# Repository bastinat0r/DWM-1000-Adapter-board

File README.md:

# Board to Interface with DWM1000 module from Decawave

Created by Sebastian Mai under CC-BY-SA 2.0 license.

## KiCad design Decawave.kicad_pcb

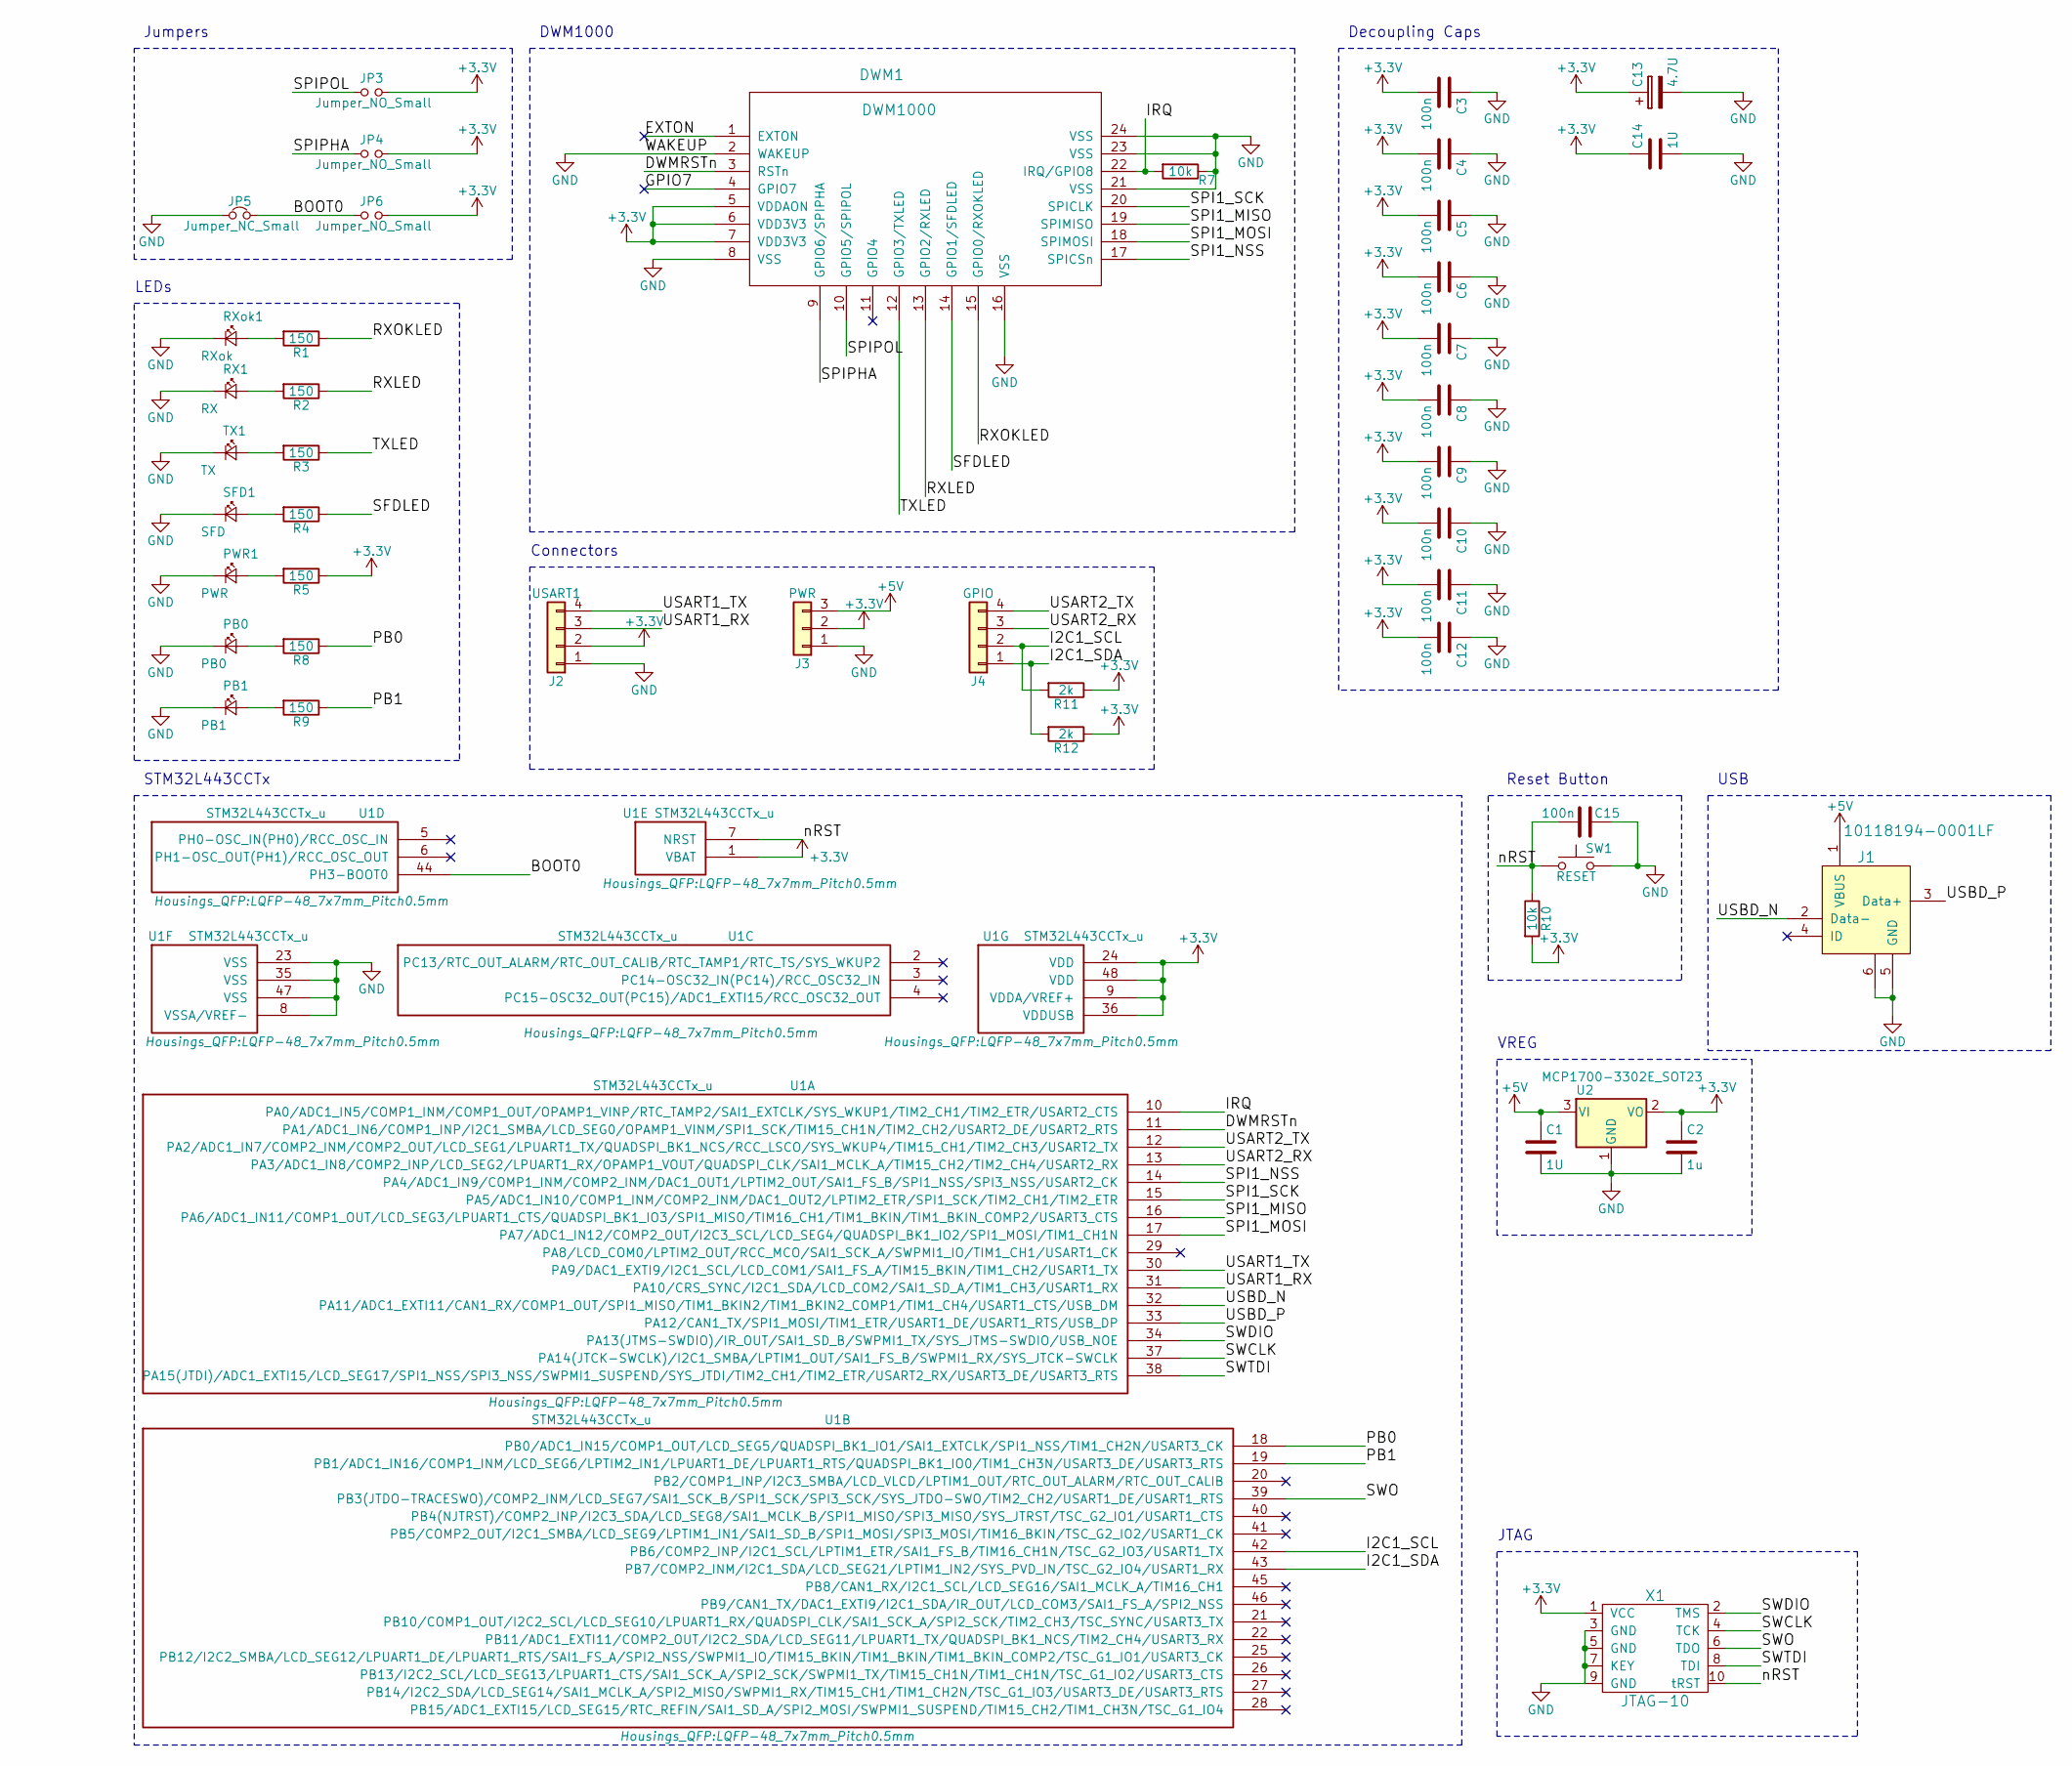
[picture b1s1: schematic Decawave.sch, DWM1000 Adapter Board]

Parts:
C1, C14: 1U; C_1206_HandSoldering
C2: 1u; C_1206_HandSoldering
C3, C4, C5, C6, C7, C8, C9, C10, C11, C12, C15: 100n; C_0603_HandSoldering
C13: 4.7U; CP_Tantalum_Case-A_EIA-3216-18_Hand
DWM1: DWM1000
J1: 10118194-0001LF; USB_Micro_B_Female_10118194-0001LF; MPN 10118194-0001LF; Digi-Key_PN 609-4618-1-ND
J2: USART1; Pin_Header_Straight_1x04_Pitch2.54mm
J3: PWR; Pin_Header_Straight_1x03_Pitch2.54mm
J4: GPIO; Pin_Header_Straight_1x04_Pitch2.54mm
JP3, JP4, JP6: Jumper_NO_Small; R_0402
JP5: Jumper_NC_Small; R_0402
PB0: PB0; LED_0805_HandSoldering
PB1: PB1; LED_0805_HandSoldering
PWR1: PWR; LED_0805_HandSoldering
R1, R2, R3, R4, R5, R8, R9: 150; R_0603_HandSoldering
R7, R10: 10k; R_0603_HandSoldering
R11, R12: 2k; R_0603_HandSoldering
RX1: RX; LED_0805_HandSoldering
RXok1: RXok; LED_0805_HandSoldering
SFD1: SFD; LED_0805_HandSoldering
SW1: RESET; SW_SPST_TL3342
TX1: TX; LED_0805_HandSoldering
U1: STM32L443CCTx_u; LQFP-48_7x7mm_Pitch0.5mm
U2: MCP1700-3302E_SOT23; SOT-23_Handsoldering
X1: JTAG-10; FTSH-105-XX-X-DV

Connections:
+3V3: C2.1, C3.2, C4.2, C5.2, C6.2, C7.2, C8.2, C9.2, C10.2, C11.2, C12.2, C13.1, C14.1, DWM1.5 (VDDAON), DWM1.6 (VDD3V3), DWM1.7 (VDD3V3), J2.2, J3.2, JP3.2, JP4.2, JP6.2, R5.1, R10.2, R11.1, R12.1, U1.1 (VBAT), U1.9 (VDDA/VREF+), U1.24 (VDD), U1.36 (VDDUSB), U1.48 (VDD), U2.2 (VO), X1.1 (VCC)
+5V: C1.1, J1.1 (VBUS), J3.3, U2.3 (VI)
/BOOT0: JP5.2, JP6.1, U1.44 (PH3-BOOT0)
/DWMRSTn: DWM1.3 (RSTn), U1.11 (PA1/ADC1_IN6/COMP1_INP/I2C1_SMBA/LCD_SE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)
/EXTON: DWM1.1 (EXTON)
/GPIO7: DWM1.4 (GPIO7)
/I2C1_SCL: J4.2, R11.2, U1.42 (PB6/COMP2_INP/I2C1_SCL/LPTIM1_ETR/SAI1_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)
/I2C1_SDA: J4.1, R12.2, U1.43 (PB7/COMP2_INM/I2C1_SDA/LCD_SEG21/LPTIM1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)
/IRQ: DWM1.22 (IRQ/GPIO8), R7.2, U1.10 (PA0/ADC1_IN5/COMP1_INM/COMP1_OUT/OPAMP1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)
/PB0: R8.1, U1.18 (PB0/ADC1_IN15/COMP1_OUT/LCD_SEG5/QUADSP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)
/PB1: R9.1, U1.19 (PB1/ADC1_IN16/COMP1_INM/LCD_SEG6/LPTIM2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)
/RXLED: DWM1.13 (GPIO2/RXLED), R2.1
/RXOKLED: DWM1.15 (GPIO0/RXOKLED), R1.1
/SFDLED: DWM1.14 (GPIO1/SFDLED), R4.1
/SPI1_MISO: DWM1.19 (SPIMISO), U1.16 (PA6/ADC1_IN11/COMP1_OUT/LCD_SEG3/LPUART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)
/SPI1_MOSI: DWM1.18 (SPIMOSI), U1.17 (PA7/ADC1_IN12/COMP2_OUT/I2C3_SCL/LCD_SE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)
/SPI1_NSS: DWM1.17 (SPICSn), U1.14 (PA4/ADC1_IN9/COMP1_INM/COMP2_INM/DAC1_O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)
/SPI1_SCK: DWM1.20 (SPICLK), U1.15 (PA5/ADC1_IN10/COMP1_INM/COMP2_INM/DAC1_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)
/SPIPHA: DWM1.9 (GPIO6/SPIPHA), JP4.1
/SPIPOL: DWM1.10 (GPIO5/SPIPOL), JP3.1
/SWCLK: U1.37 (PA14(JTCK-SWCLK)/I2C1_SMBA/LPTIM1_OUT/S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), X1.4 (TCK)
/SWDIO: U1.34 (PA13(JTMS-SWDIO)/IR_OUT/SAI1_SD_B/SWPMI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), X1.2 (TMS)
/SWO: U1.39 (PB3(JTDO-TRACESWO)/COMP2_INM/LCD_SEG7/S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), X1.6 (TDO)
/SWTDI: U1.38 (PA15(JTDI)/ADC1_EXTI15/LCD_SEG17/SPI1_N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), X1.8 (TDI)
/TXLED: DWM1.12 (GPIO3/TXLED), R3.1
/USART1_RX: J2.3, U1.31 (PA10/CRS_SYNC/I2C1_SDA/LCD_COM2/SAI1_SD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)
/USART1_TX: J2.4, U1.30 (PA9/DAC1_EXTI9/I2C1_SCL/LCD_COM1/SAI1_F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)
/USART2_RX: J4.3, U1.13 (PA3/ADC1_IN8/COMP2_INP/LCD_SEG2/LPUART1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)
/USART2_TX: J4.4, U1.12 (PA2/ADC1_IN7/COMP2_INM/COMP2_OUT/LCD_SE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)
/USBD_N: J1.2 (Data-), U1.32 (PA11/ADC1_EXTI11/CAN1_RX/COMP1_OUT/SPI1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)
/USBD_P: J1.3 (Data+), U1.33 (PA12/CAN1_TX/SPI1_MOSI/TIM1_ETR/USART1_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)
/nRST: C15.2, R10.1, SW1.1, U1.7 (NRST), X1.10 (tRST)
GND: C1.2, C2.2, C3.1, C4.1, C5.1, C6.1, C7.1, C8.1, C9.1, C10.1, C11.1, C12.1, C13.2, C14.2, C15.1, DWM1.2 (WAKEUP), DWM1.8 (VSS), DWM1.16 (VSS), DWM1.21 (VSS), DWM1.23 (VSS), DWM1.24 (VSS), J1.5 (GND), J1.6, J2.1, J3.1, JP5.1, PB0.1 (K), PB1.1 (K), PWR1.1 (K), R7.1, RX1.1 (K), RXok1.1 (K), SFD1.1 (K), SW1.2, TX1.1 (K), U1.8 (VSSA/VREF-), U1.23 (VSS), U1.35 (VSS), U1.47 (VSS), U2.1 (GND), X1.3 (GND), X1.5 (GND), X1.7 (KEY), X1.9 (GND)
unnamed: PB0.2 (A), R8.2
unnamed: PB1.2 (A), R9.2
unnamed: PWR1.2 (A), R5.2
unnamed: R1.2, RXok1.2 (A)
unnamed: R2.2, RX1.2 (A)
unnamed: R3.2, TX1.2 (A)
unnamed: R4.2, SFD1.2 (A)

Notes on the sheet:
Jumpers
LEDs
JTAG
Reset Button
USB
VREG
Connectors
DWM1000
Decoupling Caps
STM32L443CCTx

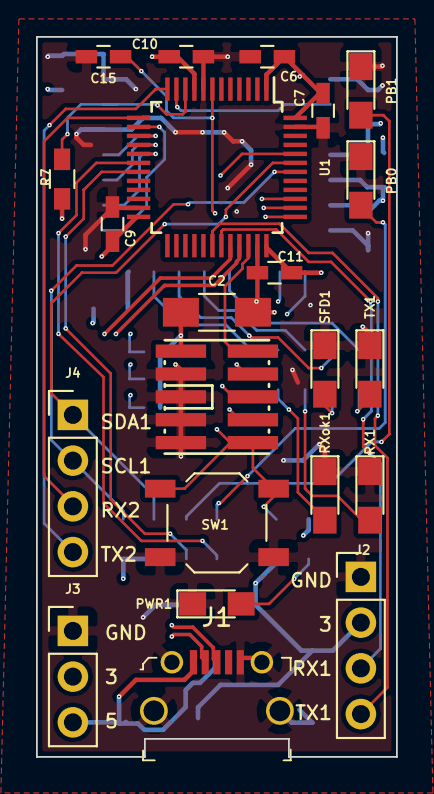
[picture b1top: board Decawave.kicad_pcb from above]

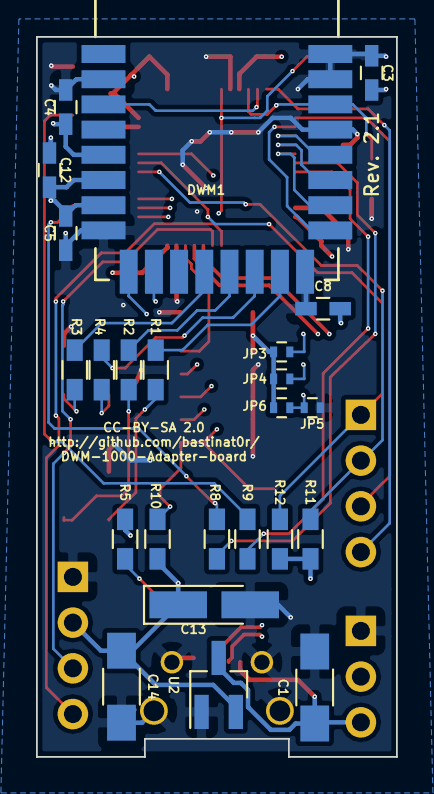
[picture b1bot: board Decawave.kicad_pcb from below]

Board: 4 copper layers, 20.0 x 40.0 mm, 46 parts (24 on the bottom side), 38 nets.

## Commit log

2017-10-17 inital commit
2017-10-17 adding readme
2017-10-17 adding 100n Cap for nRST
2017-10-17 Reorganising Schematic
2017-10-17 add url to gh repo on pcb
2017-10-18 Some ground-plane improvements
2017-10-18 even more gnd plane improvements
2017-10-18 remove unecessary jumpers
    * spipol and spipha are internally pulled low by the DWM1000
2017-10-18 moving usb port closer to the edge
2017-10-31 fixing text for print-out assembly instructions
2017-11-15 Moving trace away from the edge of the board
2018-03-15 usb footprint, route usb as differential pair
2018-05-02 adding silkscreen for pins
2018-05-14 adding more space for usb connector
2018-05-14 adding modified micro usb (slots -> holes)
